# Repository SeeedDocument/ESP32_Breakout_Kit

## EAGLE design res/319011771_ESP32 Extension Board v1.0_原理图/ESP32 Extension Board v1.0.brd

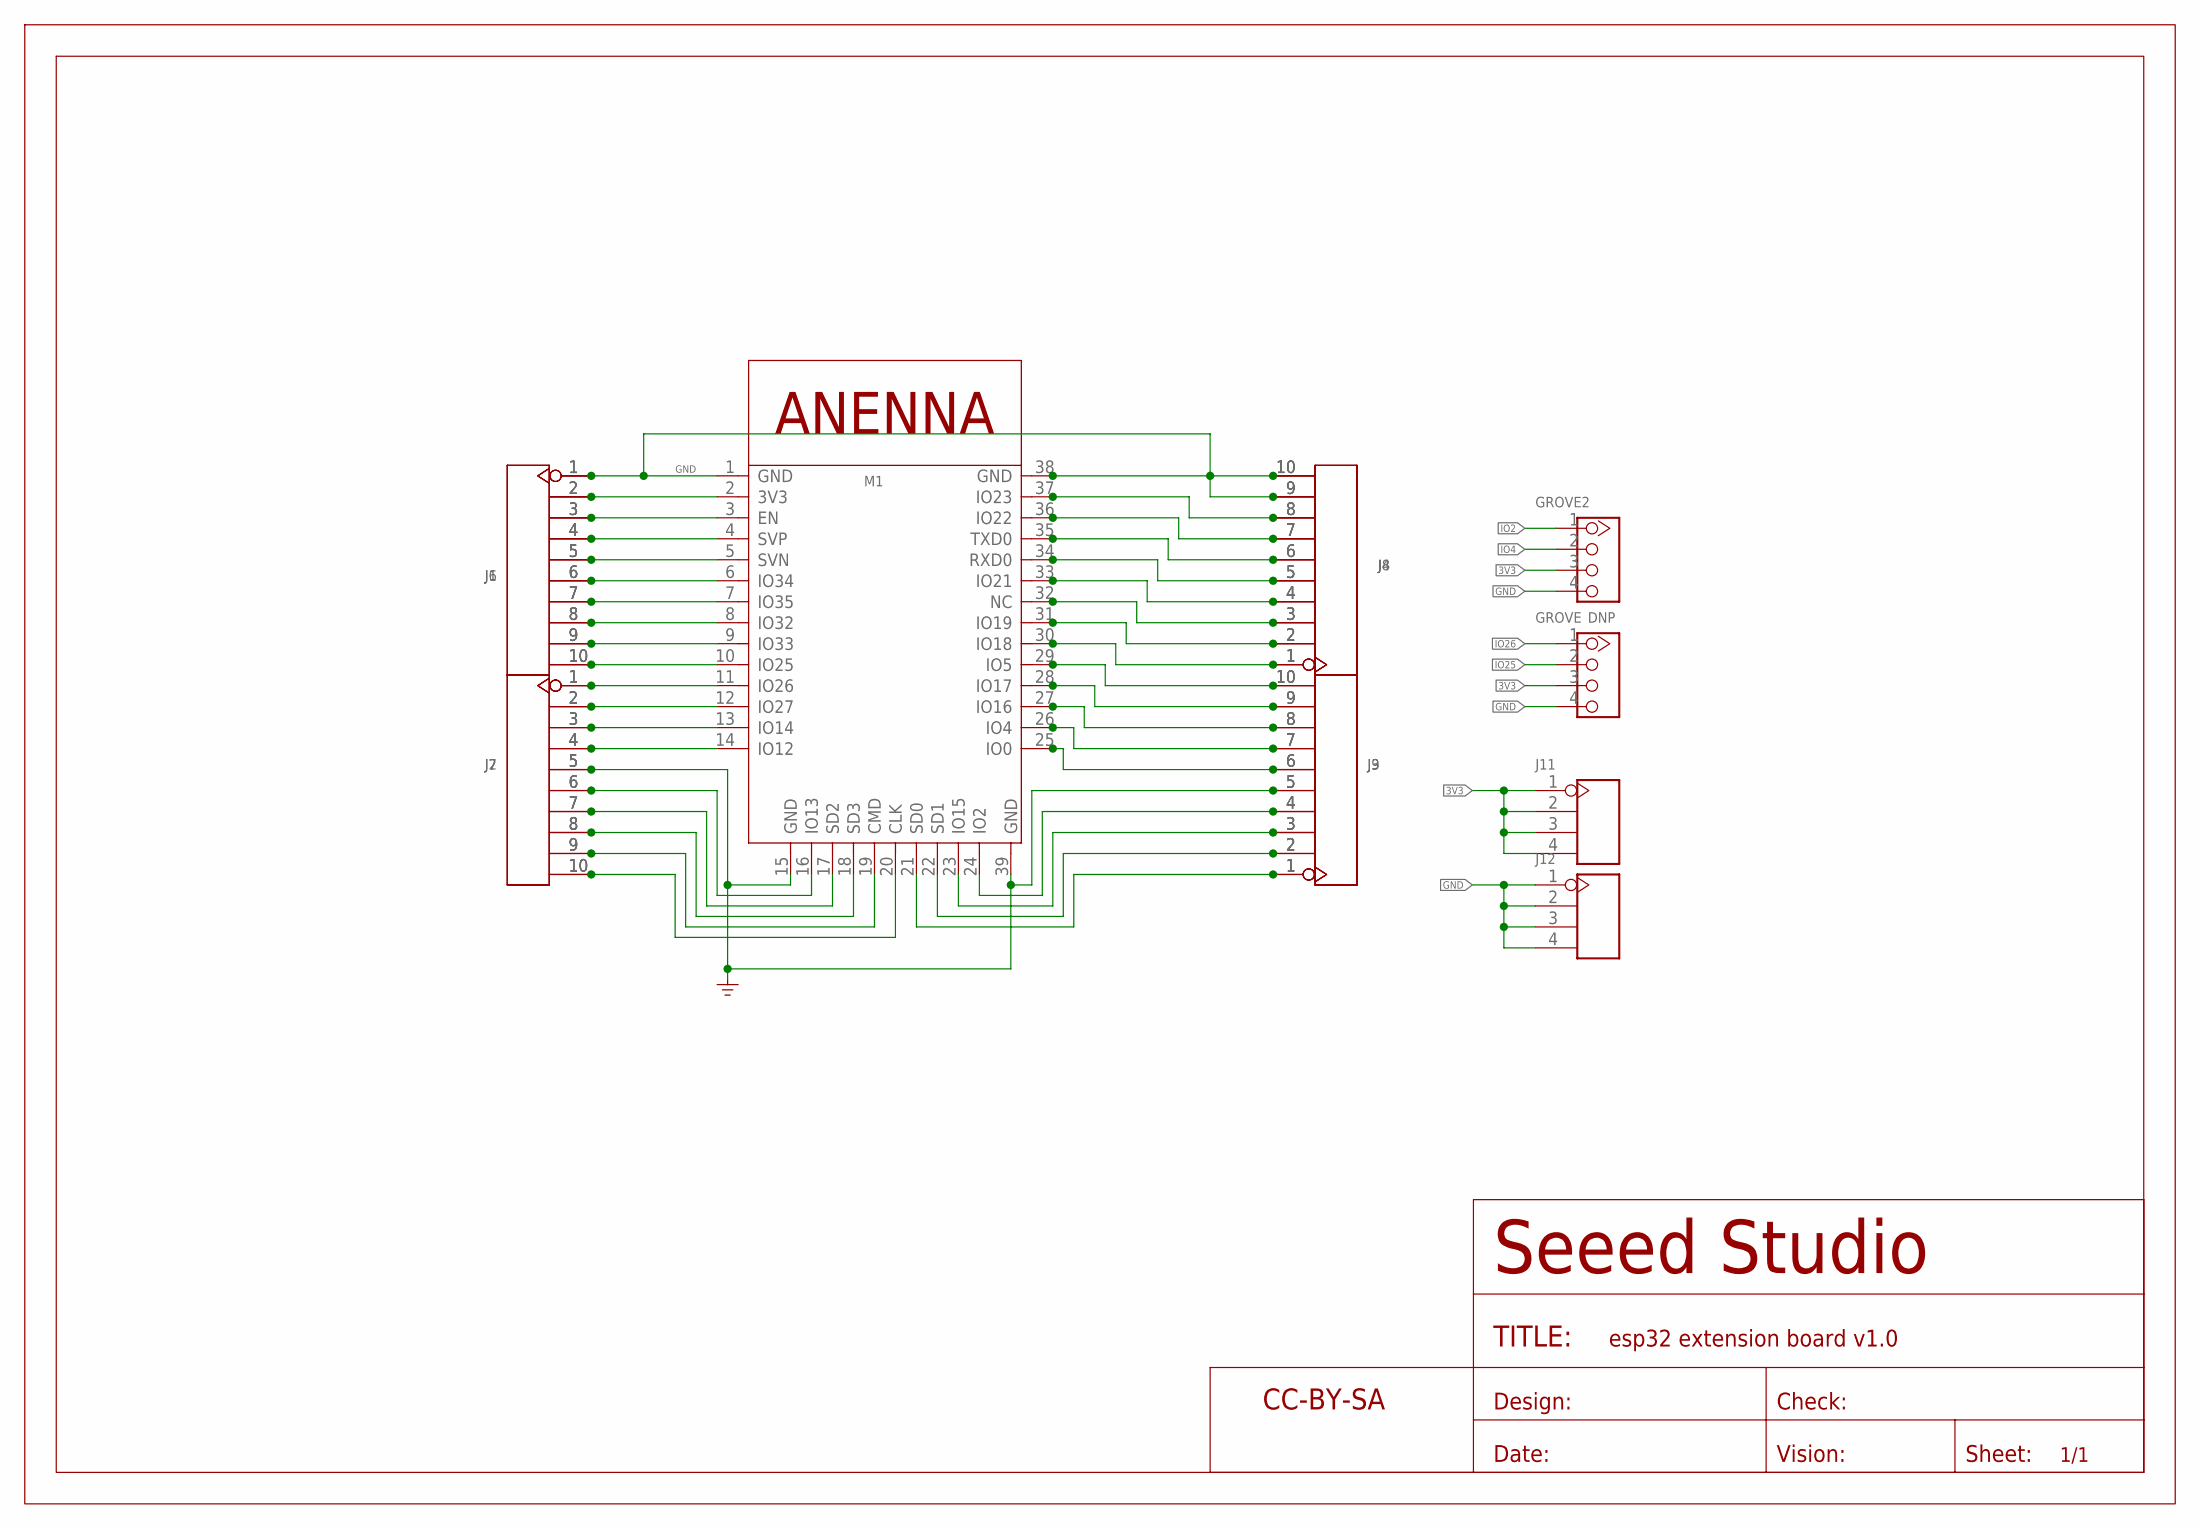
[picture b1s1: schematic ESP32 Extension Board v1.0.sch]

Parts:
FR2: SEEEDSTUDIO-OPEN-SCH-FRAME; SEEEDSTUDIO-PCB-FRAME
GROVE: DNP; HW4-2.0
GROVE2: GROVE-CONNECTOR-DIP-2.0; HW4-2.0
J1, J2, J3, J4, J6, J7, J8, J9: HEADER-10P-2.54; H10-2.54
J11, J12: HEADER-4P-65/35MIL; H4-2.54
M1: MODULE-WIFI-ESP-3212-38+1; MODULE38P-1.3-18X25.5MM

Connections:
3V3: GROVE.3, GROVE2.3, J1.2, J6.2, J11.1, J11.2, J11.3, J11.4, M1.2 (3V3)
CLK: J2.10, J7.10, M1.20 (CLK)
CMD: J2.9, J7.9, M1.19 (CMD)
EN: J1.3, J6.3, M1.3 (EN)
GND: GROVE.4, GROVE2.4, J1.1, J2.5, J3.5, J4.9, J4.10, J6.1, J7.5, J8.9, J8.10, J9.5, J12.1, J12.2, J12.3, J12.4, M1.1 (GND), M1.15 (GND), M1.38 (GND), M1.39 (GND)
IO0: J3.6, J9.6, M1.25 (IO0)
IO2: GROVE2.1, J3.4, J9.4, M1.24 (IO2)
IO4: GROVE2.2, J3.7, J9.7, M1.26 (IO4)
IO5: J3.10, J9.10, M1.29 (IO5)
IO12: J2.4, J7.4, M1.14 (IO12)
IO13: J2.6, J7.6, M1.16 (IO13)
IO14: J2.3, J7.3, M1.13 (IO14)
IO15: J3.3, J9.3, M1.23 (IO15)
IO16: J3.8, J9.8, M1.27 (IO16)
IO17: J3.9, J9.9, M1.28 (IO17)
IO18: J4.1, J8.1, M1.30 (IO18)
IO19: J4.2, J8.2, M1.31 (IO19)
IO21: J4.4, J8.4, M1.33 (IO21)
IO22: J4.7, J8.7, M1.36 (IO22)
IO23: J4.8, J8.8, M1.37 (IO23)
IO25: GROVE.2, J1.10, J6.10, M1.10 (IO25)
IO26: GROVE.1, J2.1, J7.1, M1.11 (IO26)
IO27: J2.2, J7.2, M1.12 (IO27)
IO32: J1.8, J6.8, M1.8 (IO32)
IO33: J1.9, J6.9, M1.9 (IO33)
IO34: J1.6, J6.6, M1.6 (IO34)
IO35: J1.7, J6.7, M1.7 (IO35)
NC: J4.3, J8.3, M1.32 (NC)
RXD0: J4.5, J8.5, M1.34 (RXD0)
SD0: J3.1, J9.1, M1.21 (SD0)
SD1: J3.2, J9.2, M1.22 (SD1)
SD2: J2.7, J7.7, M1.17 (SD2)
SD3: J2.8, J7.8, M1.18 (SD3)
SVN: J1.5, J6.5, M1.5 (SVN)
SVP: J1.4, J6.4, M1.4 (SVP)
TXD0: J4.6, J8.6, M1.35 (TXD0)

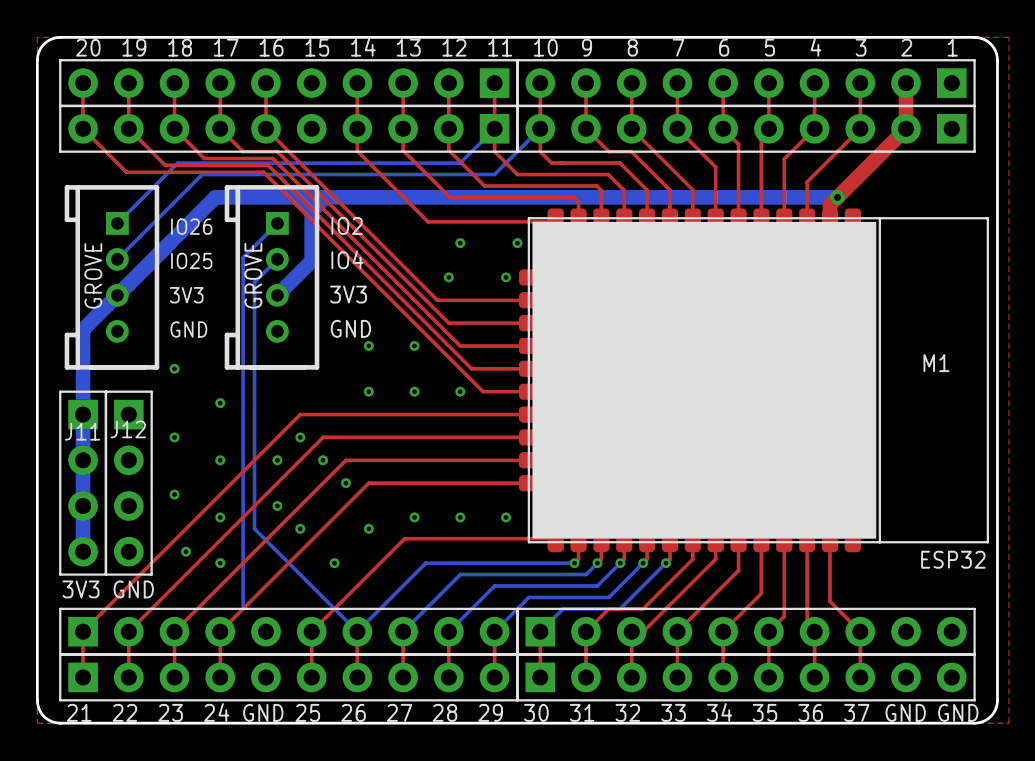
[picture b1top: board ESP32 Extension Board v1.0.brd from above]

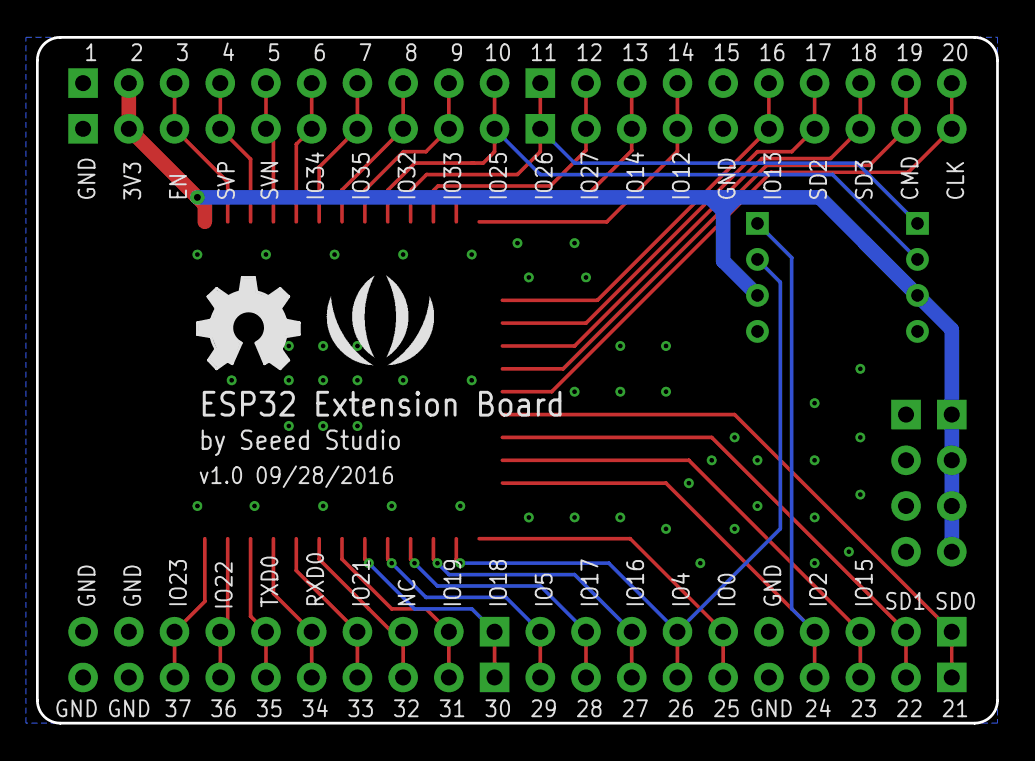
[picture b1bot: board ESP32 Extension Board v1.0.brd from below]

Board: 2 copper layers, 53.3 x 38.1 mm, 16 parts (2 on the bottom side), 36 nets.

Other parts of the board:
U$1: OSHW_FILLX200_NOTEXT
U$3: SEEED-SILK-280*268MIL

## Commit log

2016-12-30 add img&res
2016-12-30 update images
2016-12-30 add pinmap
2017-04-06 add pcb.pdf
2017-04-06 add esp32
2019-11-05 add
    add

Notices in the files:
parts and their libraries:
moudle-new: This work is licensed under the Creative Commons Attribution 4.0 International License.
To view a copy of this license,visit:
http://creativecommons.org/licenses/by-sa/4.0
moudle-new: CC-BY-SA
